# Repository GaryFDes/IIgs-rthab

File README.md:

# IIgs RGBToHDMI Adaptor Board
ROM 01 Apple IIgs RGBToHDMI Adapter board [Top](pictures/Top%20of%20Board.jpeg)/[Bottom](pictures/Bottom%20of%20Board.jpeg)

[Plug](https://warwickts.com/4405/W9327-68-Way-PLCC-Plug) that I used and bought there.

[Socket](https://app.adam-tech.com/products/download/data_sheet/198229/plcc-68-at-data-sheet.pdf) that I used and bought on [DigiKey](https://www.digikey.com/en/products/detail/adam-tech/PLCC-68-AT/9833042)

This is my fourth revision of this board:

* Revision 1 - The board needed the post through it (never sent this to the fab).
* Revision 2 - The traces were wired incorrectly.
* Revision 3 - The board was too big because the board had to be lower and then had to clear not only the post but the big capacitor.
* Revision 4 - This board.

I originally wanted to have the plug and socket on the bottom, and [this connection header](https://www.digikey.com/en/products/detail/te-connectivity-amp-connectors/5103308-3/1114901) on the top.  I found out in the end that I needed to solder the cable right to the header in order to have the height correct.  Also, the plug described above was too tall.  I had to cut down the plug one layer.  There is another [low height connector](https://us.warwickts.com/4391/W9305-68-Way-PLCC-Plug) that is through hole but sold only in bulk.  If I ever get enough gumption and money I will try to redesign the card with that plug in mind.

Steps are:
1) Get all the supplies (plug and PLCC68 socket).
2) Get the board(s).
3) Get (or build) an RGBToHDMI and the associated 12 bit card.
4) Cut down the plug (not an easy task).
5) Surface mount the plug.
6) Through hold solder the socket.
7) Connect the cable that is long enough to go through the opening on the IIgs.
8) Unplug the VGC (I suggest a good puller) and insert the VGC into the socket on the board. I used [this](https://www.amazon.com/dp/B00FZPSRGE)
9) Connect your RGBToHDMI 12 bit connector to the cable (!!DO NOT!! Supply power to the RGBToHDMI.  The IIgs cable already has power on it.)
10) Connect to your HDMI monitor.

I included the ROM 03 IIgs Kicad stuff because I only used a [socket](https://www.amazon.com/dp/B0C7GGJW49) over the top of the present VGC which is soldered to the motherboard. The pinout I originally did for the ROM 03 IIgs.
12) Start up the monitor and the IIgs.

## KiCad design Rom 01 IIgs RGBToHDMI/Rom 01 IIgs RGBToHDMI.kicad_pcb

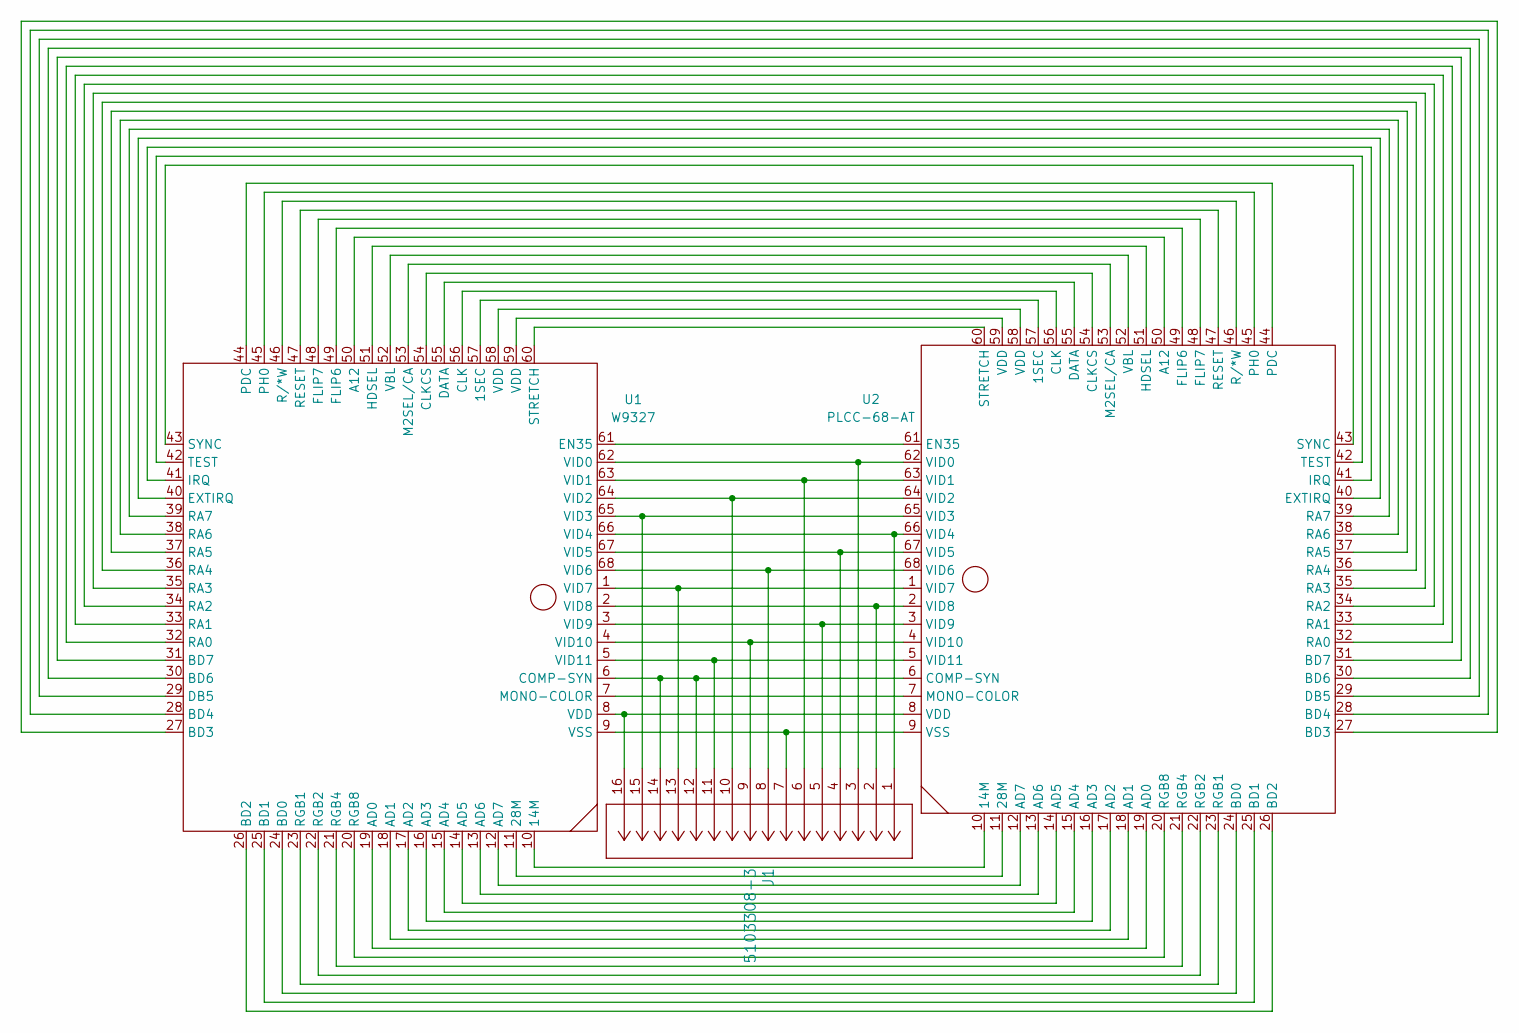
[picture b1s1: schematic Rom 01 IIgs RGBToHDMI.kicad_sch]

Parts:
J1: 5103308-3; con16_2X8_S4_TEC
U1: W9327; Winslow W9327
U2: PLCC-68-AT

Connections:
unnamed: J1.16, U1.8 (VDD), U2.8 (VDD)
unnamed: U1.57 (1SEC), U2.57 (1SEC)
unnamed: U1.10 (14M), U2.10 (14M)
unnamed: U1.11 (28M), U2.11 (28M)
unnamed: U1.50 (A12), U2.50 (A12)
unnamed: U1.19 (AD0), U2.19 (AD0)
unnamed: U1.18 (AD1), U2.18 (AD1)
unnamed: U1.17 (AD2), U2.17 (AD2)
unnamed: U1.16 (AD3), U2.16 (AD3)
unnamed: U1.15 (AD4), U2.15 (AD4)
unnamed: U1.14 (AD5), U2.14 (AD5)
unnamed: U1.13 (AD6), U2.13 (AD6)
unnamed: U1.12 (AD7), U2.12 (AD7)
unnamed: U1.24 (BD0), U2.24 (BD0)
unnamed: U1.25 (BD1), U2.25 (BD1)
unnamed: U1.26 (BD2), U2.26 (BD2)
unnamed: U1.27 (BD3), U2.27 (BD3)
unnamed: U1.28 (BD4), U2.28 (BD4)
unnamed: U1.30 (BD6), U2.30 (BD6)
unnamed: U1.31 (BD7), U2.31 (BD7)
unnamed: U1.56 (CLK), U2.56 (CLK)
unnamed: U1.54 (CLKCS), U2.54 (CLKCS)
unnamed: J1.12, J1.14, U1.6 (COMP-SYN), U2.6 (COMP-SYN)
unnamed: U1.55 (DATA), U2.55 (DATA)
unnamed: U1.29 (DB5), U2.29 (DB5)
unnamed: U1.61 (EN35), U2.61 (EN35)
unnamed: U1.40 (EXTIRQ), U2.40 (EXTIRQ)
unnamed: U1.49 (FLIP6), U2.49 (FLIP6)
unnamed: U1.48 (FLIP7), U2.48 (FLIP7)
unnamed: U1.51 (HDSEL), U2.51 (HDSEL)
unnamed: U1.41 (IRQ), U2.41 (IRQ)
unnamed: U1.53 (M2SEL/CA), U2.53 (M2SEL/CA)
unnamed: U1.7 (MONO-COLOR), U2.7 (MONO-COLOR)
unnamed: U1.44 (PDC), U2.44 (PDC)
unnamed: U1.45 (PH0), U2.45 (PH0)
unnamed: U1.32 (RA0), U2.32 (RA0)
unnamed: U1.33 (RA1), U2.33 (RA1)
unnamed: U1.34 (RA2), U2.34 (RA2)
unnamed: U1.35 (RA3), U2.35 (RA3)
unnamed: U1.36 (RA4), U2.36 (RA4)
unnamed: U1.37 (RA5), U2.37 (RA5)
unnamed: U1.38 (RA6), U2.38 (RA6)
unnamed: U1.39 (RA7), U2.39 (RA7)
unnamed: U1.47 (RESET), U2.47 (RESET)
unnamed: U1.23 (RGB1), U2.23 (RGB1)
unnamed: U1.22 (RGB2), U2.22 (RGB2)
unnamed: U1.21 (RGB4), U2.21 (RGB4)
unnamed: U1.20 (RGB8), U2.20 (RGB8)
unnamed: U1.46 (R/*W), U2.46 (R/*W)
unnamed: U1.60 (STRETCH), U2.60 (STRETCH)
unnamed: U1.43 (SYNC), U2.43 (SYNC)
unnamed: U1.42 (TEST), U2.42 (TEST)
unnamed: U1.52 (VBL), U2.52 (VBL)
unnamed: U1.58 (VDD), U2.58 (VDD)
unnamed: U1.59 (VDD), U2.59 (VDD)
unnamed: J1.3, U1.62 (VID0), U2.62 (VID0)
unnamed: J1.6, U1.63 (VID1), U2.63 (VID1)
unnamed: J1.10, U1.64 (VID2), U2.64 (VID2)
unnamed: J1.15, U1.65 (VID3), U2.65 (VID3)
unnamed: J1.1, U1.66 (VID4), U2.66 (VID4)
unnamed: J1.4, U1.67 (VID5), U2.67 (VID5)
unnamed: J1.8, U1.68 (VID6), U2.68 (VID6)
unnamed: J1.13, U1.1 (VID7), U2.1 (VID7)
unnamed: J1.2, U1.2 (VID8), U2.2 (VID8)
unnamed: J1.5, U1.3 (VID9), U2.3 (VID9)
unnamed: J1.9, U1.4 (VID10), U2.4 (VID10)
unnamed: J1.11, U1.5 (VID11), U2.5 (VID11)
unnamed: J1.7, U1.9 (VSS), U2.9 (VSS)

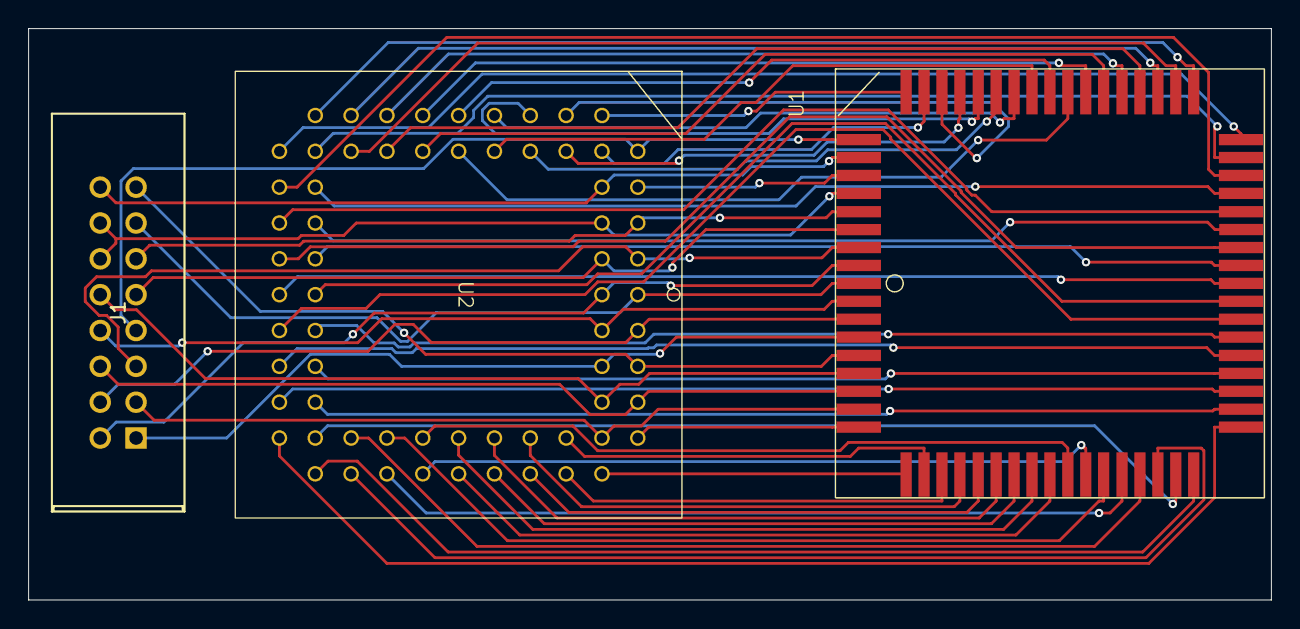
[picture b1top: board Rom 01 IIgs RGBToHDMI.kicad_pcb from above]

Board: 2 copper layers, 88.1 x 40.5 mm, 3 parts (0 on the bottom side), 68 nets.

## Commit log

2024-05-25 Real first commit
    These are the files I originally have for the board I created.
2024-05-25 ROM 03 IIgs Files
    Files from my Rom 03 IIgs RGBToHDMI cap I created.
    I did not produce a board for these. See the image,
2024-05-25 Add some pictures
    Some pictures I took while working on the system.
2024-05-25 Board Pictures
    Just a couple of quick pictures of the board.
2024-05-25 Picture of ROM 03 cap
    What it looked like when the cap was put on the IIgs VGC.
2024-05-25 Fix a couple of pictures
    Board pictures should not be so big and only have the board on them.
